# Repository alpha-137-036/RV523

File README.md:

# RV523
An implementation of a Risc-V CPU using only discrete transistors in SOT-523 packages.

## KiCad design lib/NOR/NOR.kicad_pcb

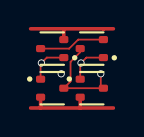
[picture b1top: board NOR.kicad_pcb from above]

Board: 2 copper layers, 4 parts (0 on the bottom side), 5 nets.

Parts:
N1, N2: SOT-523
P1, P2: SOT-523

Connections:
A: N1.1 (G), P1.1 (G)
B: N2.1 (G), P2.1 (G)
C: P1.3 (D), P2.2 (S)
GND: N1.2 (S), N2.2 (S)
Y: N1.3 (D), N2.3 (D), P2.3 (D)

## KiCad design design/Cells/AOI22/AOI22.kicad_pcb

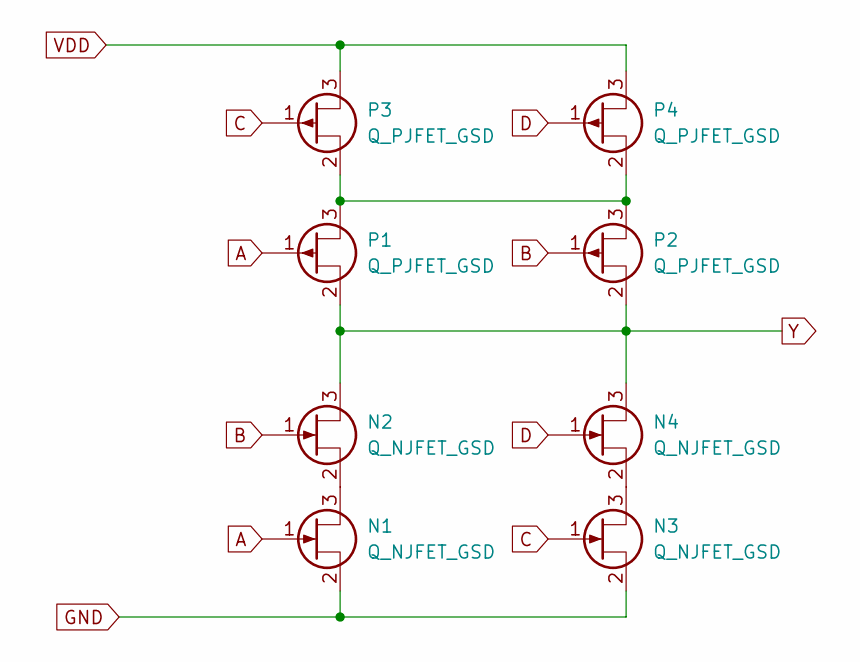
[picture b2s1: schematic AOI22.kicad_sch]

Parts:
N1, N2, N3, N4: Q_NJFET_GSD; SOT-523
P1, P2, P3, P4: Q_PJFET_GSD; SOT-523

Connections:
A: N1.1 (G), P1.1 (G)
B: N2.1 (G), P2.1 (G)
C: N3.1 (G), P3.1 (G)
D: N4.1 (G), P4.1 (G)
GND: N1.2 (S), N3.2 (S)
unnamed: N1.3 (D), N2.2 (S)
unnamed: N3.3 (D), N4.2 (S)
unnamed: P1.3 (D), P2.3 (D), P3.2 (S), P4.2 (S)
VDD: P3.3 (D), P4.3 (D)
Y: N2.3 (D), N4.3 (D), P1.2 (S), P2.2 (S)

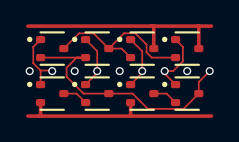
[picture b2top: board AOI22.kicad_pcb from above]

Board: 2 copper layers, 8 parts (0 on the bottom side), 10 nets.

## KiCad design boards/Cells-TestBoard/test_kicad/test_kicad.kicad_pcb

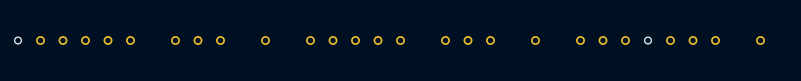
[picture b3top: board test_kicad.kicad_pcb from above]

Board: 4 copper layers, 8 parts (0 on the bottom side), 9 nets.

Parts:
XAxB: AOI22
XCin: NOT
XS: NOT
XnA: NOT
XnAxB: NOT
XnB: NOT
XnCout: AOI22
XnS: AOI22

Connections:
unnamed: XAxB.A, XnA.A, XnCout.A
unnamed: XAxB.B, XnB.A, XnCout.B
unnamed: XCin.A, XnS.B
unnamed: XAxB.C, XnA.Y
unnamed: XAxB.D, XnB.Y
unnamed: XAxB.Y, XnAxB.A, XnCout.D, XnS.A
unnamed: XCin.Y, XnCout.C, XnS.D
unnamed: XS.A, XnS.Y
unnamed: XnAxB.Y, XnS.C

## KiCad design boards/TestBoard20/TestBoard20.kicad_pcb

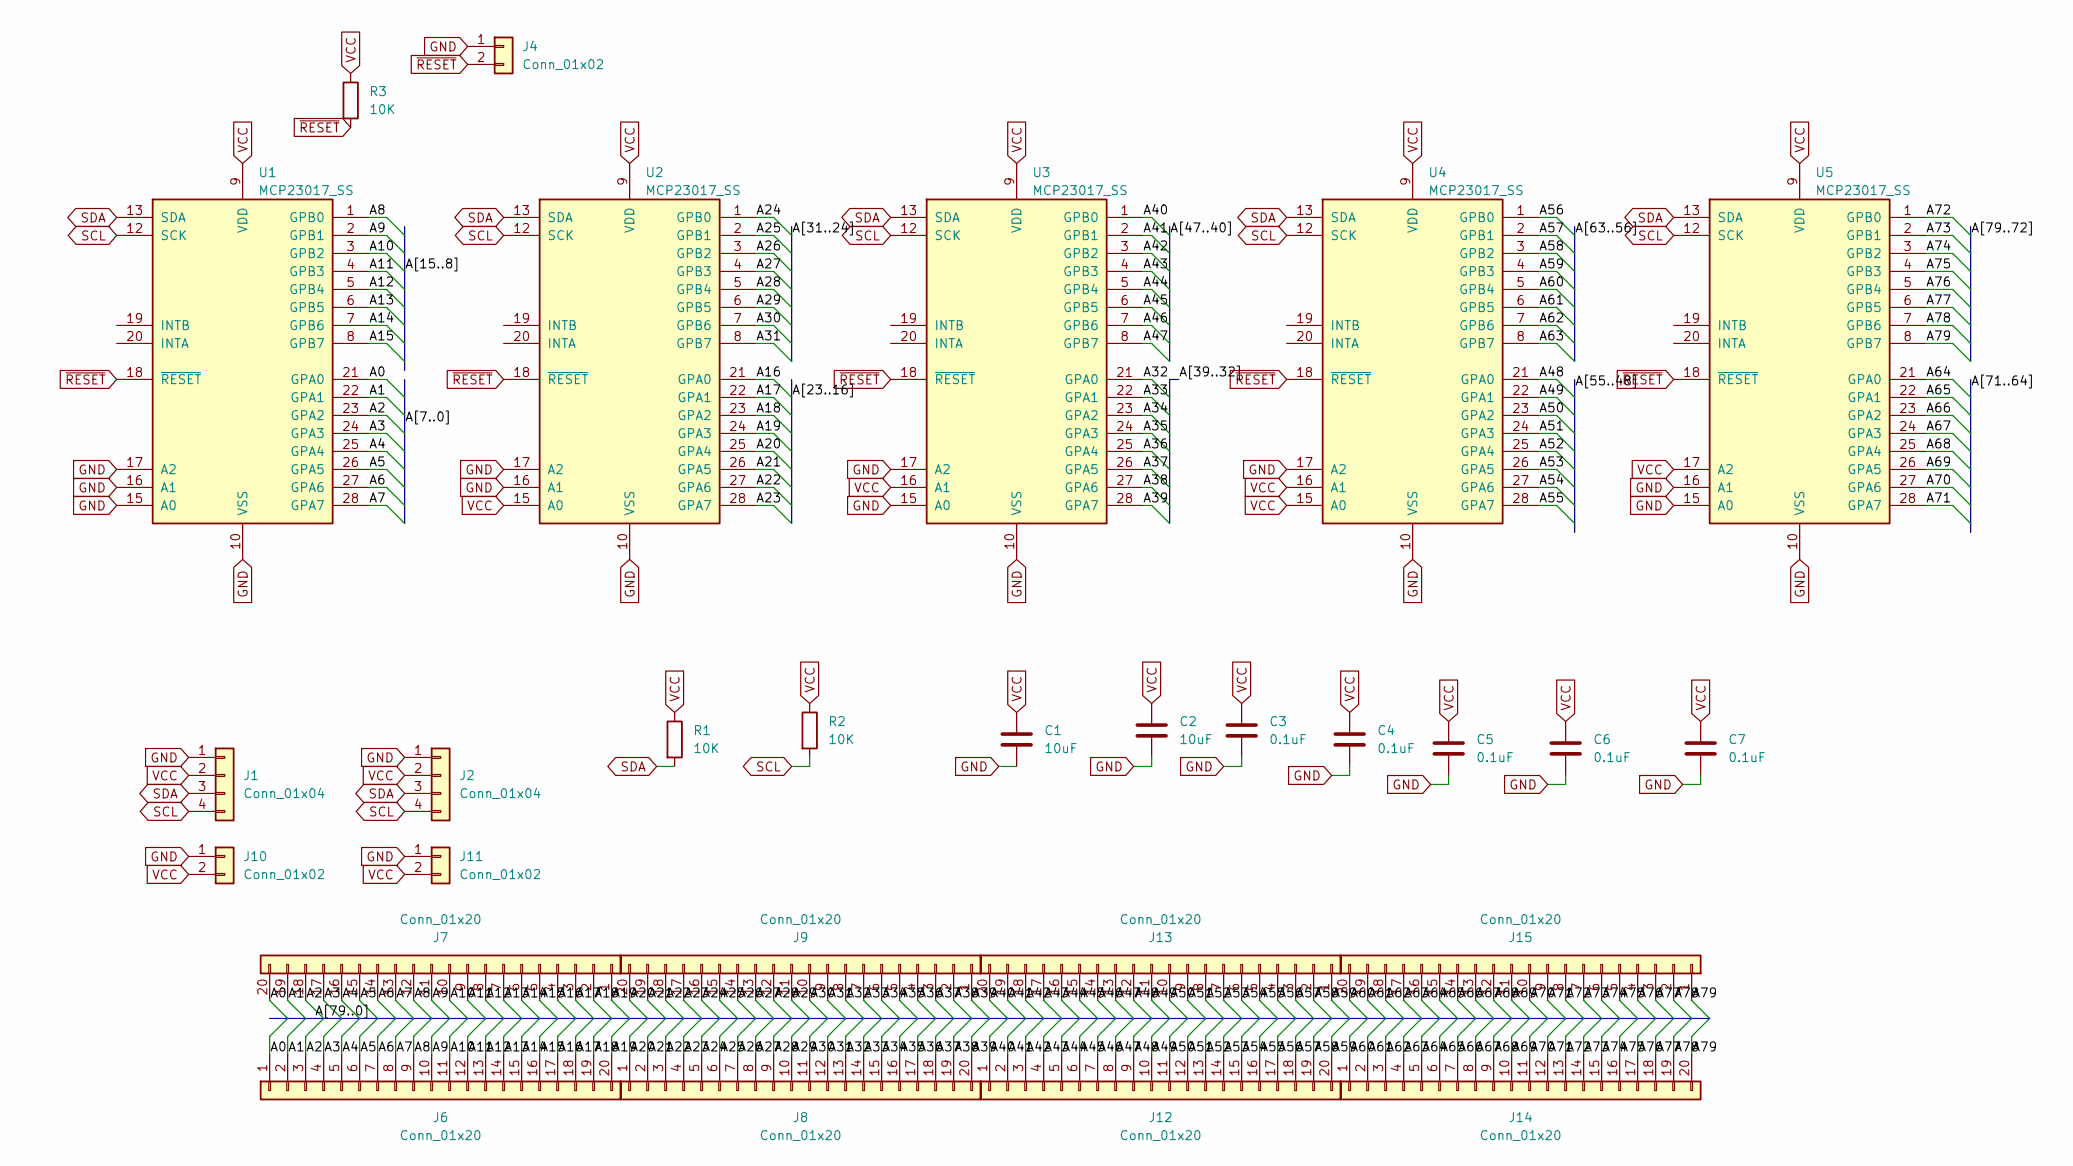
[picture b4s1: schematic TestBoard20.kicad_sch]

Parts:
C1, C2: 10uF; C_0402_1005Metric; LCSC C15525
C3, C4, C5, C6, C7: 0.1uF; C_0402_1005Metric; LCSC C1525
J1, J2: Conn_01x04; JST_SH_SM04B-SRSS-TB_1x04-1MP_P1.00mm_Horizontal; LCSC C160404
J4, J10, J11: Conn_01x02; PinHeader_1x02_P2.54mm_Vertical
J6, J7, J8, J9, J12, J13, J14, J15: Conn_01x20; FFC-SMD_FFC05021-20SBB123W5M; LCSC C19267987
R1, R2, R3: 10K; R_0402_1005Metric; LCSC C25744
U1, U2, U3, U4, U5: MCP23017_SS; SSOP-28_5.3x10.2mm_P0.65mm; LCSC C558584

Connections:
/A0: J6.1, J7.20, U1.21 (GPA0)
/A1: J6.2, J7.19, U1.22 (GPA1)
/A2: J6.3, J7.18, U1.23 (GPA2)
/A3: J6.4, J7.17, U1.24 (GPA3)
/A4: J6.5, J7.16, U1.25 (GPA4)
/A5: J6.6, J7.15, U1.26 (GPA5)
/A6: J6.7, J7.14, U1.27 (GPA6)
/A7: J6.8, J7.13, U1.28 (GPA7)
/A8: J6.9, J7.12, U1.1 (GPB0)
/A9: J6.10, J7.11, U1.2 (GPB1)
/A10: J6.11, J7.10, U1.3 (GPB2)
/A11: J6.12, J7.9, U1.4 (GPB3)
/A12: J6.13, J7.8, U1.5 (GPB4)
/A13: J6.14, J7.7, U1.6 (GPB5)
/A14: J6.15, J7.6, U1.7 (GPB6)
/A15: J6.16, J7.5, U1.8 (GPB7)
/A16: J6.17, J7.4, U2.21 (GPA0)
/A17: J6.18, J7.3, U2.22 (GPA1)
/A18: J6.19, J7.2, U2.23 (GPA2)
/A19: J6.20, J7.1, U2.24 (GPA3)
/A20: J8.1, J9.20, U2.25 (GPA4)
/A21: J8.2, J9.19, U2.26 (GPA5)
/A22: J8.3, J9.18, U2.27 (GPA6)
/A23: J8.4, J9.17, U2.28 (GPA7)
/A24: J8.5, J9.16, U2.1 (GPB0)
/A25: J8.6, J9.15, U2.2 (GPB1)
/A26: J8.7, J9.14, U2.3 (GPB2)
/A27: J8.8, J9.13, U2.4 (GPB3)
/A28: J8.9, J9.12, U2.5 (GPB4)
/A29: J8.10, J9.11, U2.6 (GPB5)
/A30: J8.11, J9.10, U2.7 (GPB6)
/A31: J8.12, J9.9, U2.8 (GPB7)
/A32: J8.13, J9.8, U3.21 (GPA0)
/A33: J8.14, J9.7, U3.22 (GPA1)
/A34: J8.15, J9.6, U3.23 (GPA2)
/A35: J8.16, J9.5, U3.24 (GPA3)
/A36: J8.17, J9.4, U3.25 (GPA4)
/A37: J8.18, J9.3, U3.26 (GPA5)
/A38: J8.19, J9.2, U3.27 (GPA6)
/A39: J8.20, J9.1, U3.28 (GPA7)
/A40: J12.1, J13.20, U3.1 (GPB0)
/A41: J12.2, J13.19, U3.2 (GPB1)
/A42: J12.3, J13.18, U3.3 (GPB2)
/A43: J12.4, J13.17, U3.4 (GPB3)
/A44: J12.5, J13.16, U3.5 (GPB4)
/A45: J12.6, J13.15, U3.6 (GPB5)
/A46: J12.7, J13.14, U3.7 (GPB6)
/A47: J12.8, J13.13, U3.8 (GPB7)
/A48: J12.9, J13.12, U4.21 (GPA0)
/A49: J12.10, J13.11, U4.22 (GPA1)
/A50: J12.11, J13.10, U4.23 (GPA2)
/A51: J12.12, J13.9, U4.24 (GPA3)
/A52: J12.13, J13.8, U4.25 (GPA4)
/A53: J12.14, J13.7, U4.26 (GPA5)
/A54: J12.15, J13.6, U4.27 (GPA6)
/A55: J12.16, J13.5, U4.28 (GPA7)
/A56: J12.17, J13.4, U4.1 (GPB0)
/A57: J12.18, J13.3, U4.2 (GPB1)
/A58: J12.19, J13.2, U4.3 (GPB2)
/A59: J12.20, J13.1, U4.4 (GPB3)
/A60: J14.1, J15.20, U4.5 (GPB4)
/A61: J14.2, J15.19, U4.6 (GPB5)
/A62: J14.3, J15.18, U4.7 (GPB6)
/A63: J14.4, J15.17, U4.8 (GPB7)
/A64: J14.5, J15.16, U5.21 (GPA0)
/A65: J14.6, J15.15, U5.22 (GPA1)
/A66: J14.7, J15.14, U5.23 (GPA2)
/A67: J14.8, J15.13, U5.24 (GPA3)
/A68: J14.9, J15.12, U5.25 (GPA4)
/A69: J14.10, J15.11, U5.26 (GPA5)
/A70: J14.11, J15.10, U5.27 (GPA6)
/A71: J14.12, J15.9, U5.28 (GPA7)
/A72: J14.13, J15.8, U5.1 (GPB0)
/A73: J14.14, J15.7, U5.2 (GPB1)
/A74: J14.15, J15.6, U5.3 (GPB2)
/A75: J14.16, J15.5, U5.4 (GPB3)
/A76: J14.17, J15.4, U5.5 (GPB4)
/A77: J14.18, J15.3, U5.6 (GPB5)
/A78: J14.19, J15.2, U5.7 (GPB6)
/A79: J14.20, J15.1, U5.8 (GPB7)
GND: C1.2, C2.2, C3.2, C4.2, C5.2, C6.2, C7.2, J1.1, J2.1, J4.1, J10.1, J11.1, U1.10 (VSS), U1.15 (A0), U1.16 (A1), U1.17 (A2), U2.10 (VSS), U2.16 (A1), U2.17 (A2), U3.10 (VSS), U3.15 (A0), U3.17 (A2), U4.10 (VSS), U4.17 (A2), U5.10 (VSS), U5.15 (A0), U5.16 (A1); also elsewhere on the board
SCL: J1.4, J2.4, R2.2, U1.12 (SCK), U2.12 (SCK), U3.12 (SCK), U4.12 (SCK), U5.12 (SCK)
SDA: J1.3, J2.3, R1.2, U1.13 (SDA), U2.13 (SDA), U3.13 (SDA), U4.13 (SDA), U5.13 (SDA)
VCC: C1.1, C2.1, C3.1, C4.1, C5.1, C6.1, C7.1, J1.2, J2.2, J10.2, J11.2, R1.1, R2.1, R3.1, U1.9 (VDD), U2.9 (VDD), U2.15 (A0), U3.9 (VDD), U3.16 (A1), U4.9 (VDD), U4.15 (A0), U4.16 (A1), U5.9 (VDD), U5.17 (A2)
~RESET: J4.2, R3.2, U1.18 (~RESET), U2.18 (~RESET), U3.18 (~RESET), U4.18 (~RESET), U5.18 (~RESET)

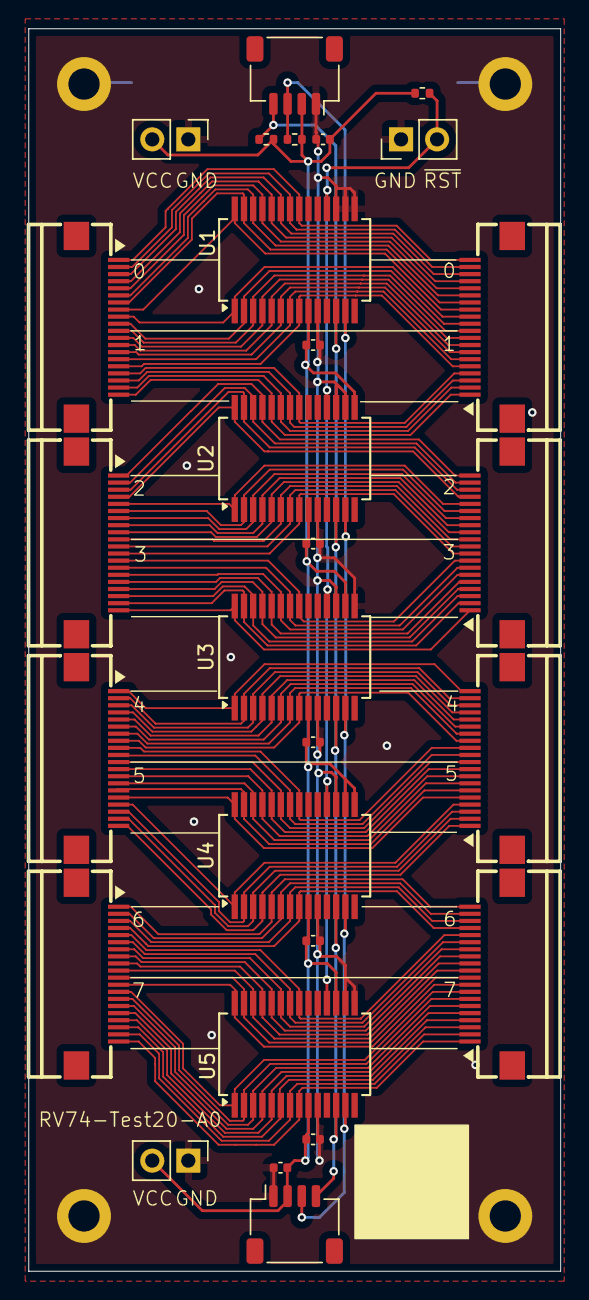
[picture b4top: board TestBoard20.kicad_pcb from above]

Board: 2 copper layers, 37.5 x 87.6 mm, 32 parts (0 on the bottom side), 85 nets.

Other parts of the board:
GND: MountingHole_2.2mm_M2_ISO14580_Pad
GND#2, GND#3, GND#4: MountingHole_2.2mm_M2_ISO14580_Pad

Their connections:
GND: GND.1, GND#2.1, GND#3.1, GND#4.1; also elsewhere on the board

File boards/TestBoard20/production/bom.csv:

Designator,Footprint,Quantity,Value,LCSC Part #
"C1, C2",0402,2,10uF,C15525
"C3, C4, C5, C6, C7",0402,5,0.1uF,C1525
"J1, J2",JST_SH_SM04B-SRSS-TB_1x04-1MP_P1.00mm_Horizontal,2,Conn_01x04,C160404
"J12, J13, J14, J15, J6, J7, J8, J9",FFC-SMD_FFC05021-20SBB123W5M,8,Conn_01x20,C19267987
"R1, R2, R3",0402,3,10K,C25744
"U1, U2, U3, U4, U5",SSOP-28_5.3x10.2mm_P0.65mm,5,MCP23017_SS,C558584

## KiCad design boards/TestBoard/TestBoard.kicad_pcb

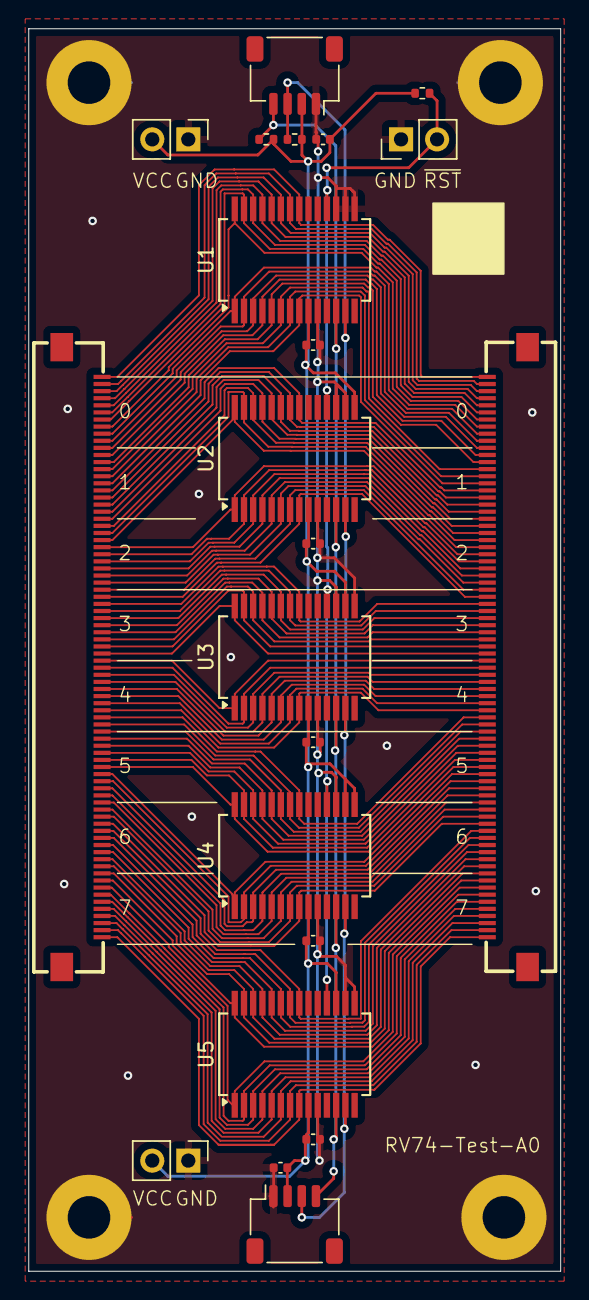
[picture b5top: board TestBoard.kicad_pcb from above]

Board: 2 copper layers, 37.5 x 87.6 mm, 26 parts (0 on the bottom side), 85 nets.

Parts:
C1, C2: 10uF; C_0402_1005Metric
C3, C4, C5, C6, C7: 0.1uF; C_0402_1005Metric
H1, H2, H3, H4: MountingHole_3mm_Pad
J1, J2: Conn_01x04; JST_SH_SM04B-SRSS-TB_1x04-1MP_P1.00mm_Horizontal
J3, J5: Conn_01x80; FPC-SMD_THD0518-80CL-GF
J4, J10, J11: Conn_01x02; PinHeader_1x02_P2.54mm_Vertical
R1, R2, R3: 10K; R_0402_1005Metric
U1, U2, U3, U4, U5: MCP23017_SS; SSOP-28_5.3x10.2mm_P0.65mm

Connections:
/A0: J3.1, J5.80, U1.21 (GPA0)
/A1: J3.2, J5.79, U1.22 (GPA1)
/A2: J3.3, J5.78, U1.23 (GPA2)
/A3: J3.4, J5.77, U1.24 (GPA3)
/A4: J3.5, J5.76, U1.25 (GPA4)
/A5: J3.6, J5.75, U1.26 (GPA5)
/A6: J3.7, J5.74, U1.27 (GPA6)
/A7: J3.8, J5.73, U1.28 (GPA7)
/A8: J3.9, J5.72, U1.1 (GPB0)
/A9: J3.10, J5.71, U1.2 (GPB1)
/A10: J3.11, J5.70, U1.3 (GPB2)
/A11: J3.12, J5.69, U1.4 (GPB3)
/A12: J3.13, J5.68, U1.5 (GPB4)
/A13: J3.14, J5.67, U1.6 (GPB5)
/A14: J3.15, J5.66, U1.7 (GPB6)
/A15: J3.16, J5.65, U1.8 (GPB7)
/A16: J3.17, J5.64, U2.21 (GPA0)
/A17: J3.18, J5.63, U2.22 (GPA1)
/A18: J3.19, J5.62, U2.23 (GPA2)
/A19: J3.20, J5.61, U2.24 (GPA3)
/A20: J3.21, J5.60, U2.25 (GPA4)
/A21: J3.22, J5.59, U2.26 (GPA5)
/A22: J3.23, J5.58, U2.27 (GPA6)
/A23: J3.24, J5.57, U2.28 (GPA7)
/A24: J3.25, J5.56, U2.1 (GPB0)
/A25: J3.26, J5.55, U2.2 (GPB1)
/A26: J3.27, J5.54, U2.3 (GPB2)
/A27: J3.28, J5.53, U2.4 (GPB3)
/A28: J3.29, J5.52, U2.5 (GPB4)
/A29: J3.30, J5.51, U2.6 (GPB5)
/A30: J3.31, J5.50, U2.7 (GPB6)
/A31: J3.32, J5.49, U2.8 (GPB7)
/A32: J3.33, J5.48, U3.21 (GPA0)
/A33: J3.34, J5.47, U3.22 (GPA1)
/A34: J3.35, J5.46, U3.23 (GPA2)
/A35: J3.36, J5.45, U3.24 (GPA3)
/A36: J3.37, J5.44, U3.25 (GPA4)
/A37: J3.38, J5.43, U3.26 (GPA5)
/A38: J3.39, J5.42, U3.27 (GPA6)
/A39: J3.40, J5.41, U3.28 (GPA7)
/A40: J3.41, J5.40, U3.1 (GPB0)
/A41: J3.42, J5.39, U3.2 (GPB1)
/A42: J3.43, J5.38, U3.3 (GPB2)
/A43: J3.44, J5.37, U3.4 (GPB3)
/A44: J3.45, J5.36, U3.5 (GPB4)
/A45: J3.46, J5.35, U3.6 (GPB5)
/A46: J3.47, J5.34, U3.7 (GPB6)
/A47: J3.48, J5.33, U3.8 (GPB7)
/A48: J3.49, J5.32, U4.21 (GPA0)
/A49: J3.50, J5.31, U4.22 (GPA1)
/A50: J3.51, J5.30, U4.23 (GPA2)
/A51: J3.52, J5.29, U4.24 (GPA3)
/A52: J3.53, J5.28, U4.25 (GPA4)
/A53: J3.54, J5.27, U4.26 (GPA5)
/A54: J3.55, J5.26, U4.27 (GPA6)
/A55: J3.56, J5.25, U4.28 (GPA7)
/A56: J3.57, J5.24, U4.1 (GPB0)
/A57: J3.58, J5.23, U4.2 (GPB1)
/A58: J3.59, J5.22, U4.3 (GPB2)
/A59: J3.60, J5.21, U4.4 (GPB3)
/A60: J3.61, J5.20, U4.5 (GPB4)
/A61: J3.62, J5.19, U4.6 (GPB5)
/A62: J3.63, J5.18, U4.7 (GPB6)
/A63: J3.64, J5.17, U4.8 (GPB7)
/A64: J3.65, J5.16, U5.21 (GPA0)
/A65: J3.66, J5.15, U5.22 (GPA1)
/A66: J3.67, J5.14, U5.23 (GPA2)
/A67: J3.68, J5.13, U5.24 (GPA3)
/A68: J3.69, J5.12, U5.25 (GPA4)
/A69: J3.70, J5.11, U5.26 (GPA5)
/A70: J3.71, J5.10, U5.27 (GPA6)
/A71: J3.72, J5.9, U5.28 (GPA7)
/A72: J3.73, J5.8, U5.1 (GPB0)
/A73: J3.74, J5.7, U5.2 (GPB1)
/A74: J3.75, J5.6, U5.3 (GPB2)
/A75: J3.76, J5.5, U5.4 (GPB3)
/A76: J3.77, J5.4, U5.5 (GPB4)
/A77: J3.78, J5.3, U5.6 (GPB5)
/A78: J3.79, J5.2, U5.7 (GPB6)
/A79: J3.80, J5.1, U5.8 (GPB7)
GND: C1.2, C2.2, C3.2, C4.2, C5.2, C6.2, C7.2, H1.1, H2.1, H3.1, H4.1, J1.1, J2.1, J4.1, J10.1, J11.1, U1.10 (VSS), U1.15 (A0), U1.16 (A1), U1.17 (A2), U2.10 (VSS), U2.16 (A1), U2.17 (A2), U3.10 (VSS), U3.15 (A0), U3.17 (A2), U4.10 (VSS), U4.17 (A2), U5.10 (VSS), U5.15 (A0), U5.16 (A1)
SCL: J1.4, J2.4, R2.2, U1.12 (SCK), U2.12 (SCK), U3.12 (SCK), U4.12 (SCK), U5.12 (SCK)
SDA: J1.3, J2.3, R1.2, U1.13 (SDA), U2.13 (SDA), U3.13 (SDA), U4.13 (SDA), U5.13 (SDA)
VCC: C1.1, C2.1, C3.1, C4.1, C5.1, C6.1, C7.1, J1.2, J2.2, J10.2, J11.2, R1.1, R2.1, R3.1, U1.9 (VDD), U2.9 (VDD), U2.15 (A0), U3.9 (VDD), U3.16 (A1), U4.9 (VDD), U4.15 (A0), U4.16 (A1), U5.9 (VDD), U5.17 (A2)
~RESET: J4.2, R3.2, U1.18 (~RESET), U2.18 (~RESET), U3.18 (~RESET), U4.18 (~RESET), U5.18 (~RESET)

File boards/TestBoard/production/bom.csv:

Designator,Footprint,Quantity,Value,LCSC Part #
"C1, C2",0402,2,10uF,C15525
"C3, C4, C5, C6, C7",0402,5,0.1uF,C1525
"J1, J2",JST_SH_SM04B-SRSS-TB_1x04-1MP_P1.00mm_Horizontal,2,Conn_01x04,C160404
"J3, J5",FPC-SMD_THD0518-80CL-GF,2,Conn_01x80,C283193
"R1, R2, R3",0402,3,10K,C25744
"U1, U2, U3, U4, U5",SSOP-28_5.3x10.2mm_P0.65mm,5,MCP23017_SS,C558584

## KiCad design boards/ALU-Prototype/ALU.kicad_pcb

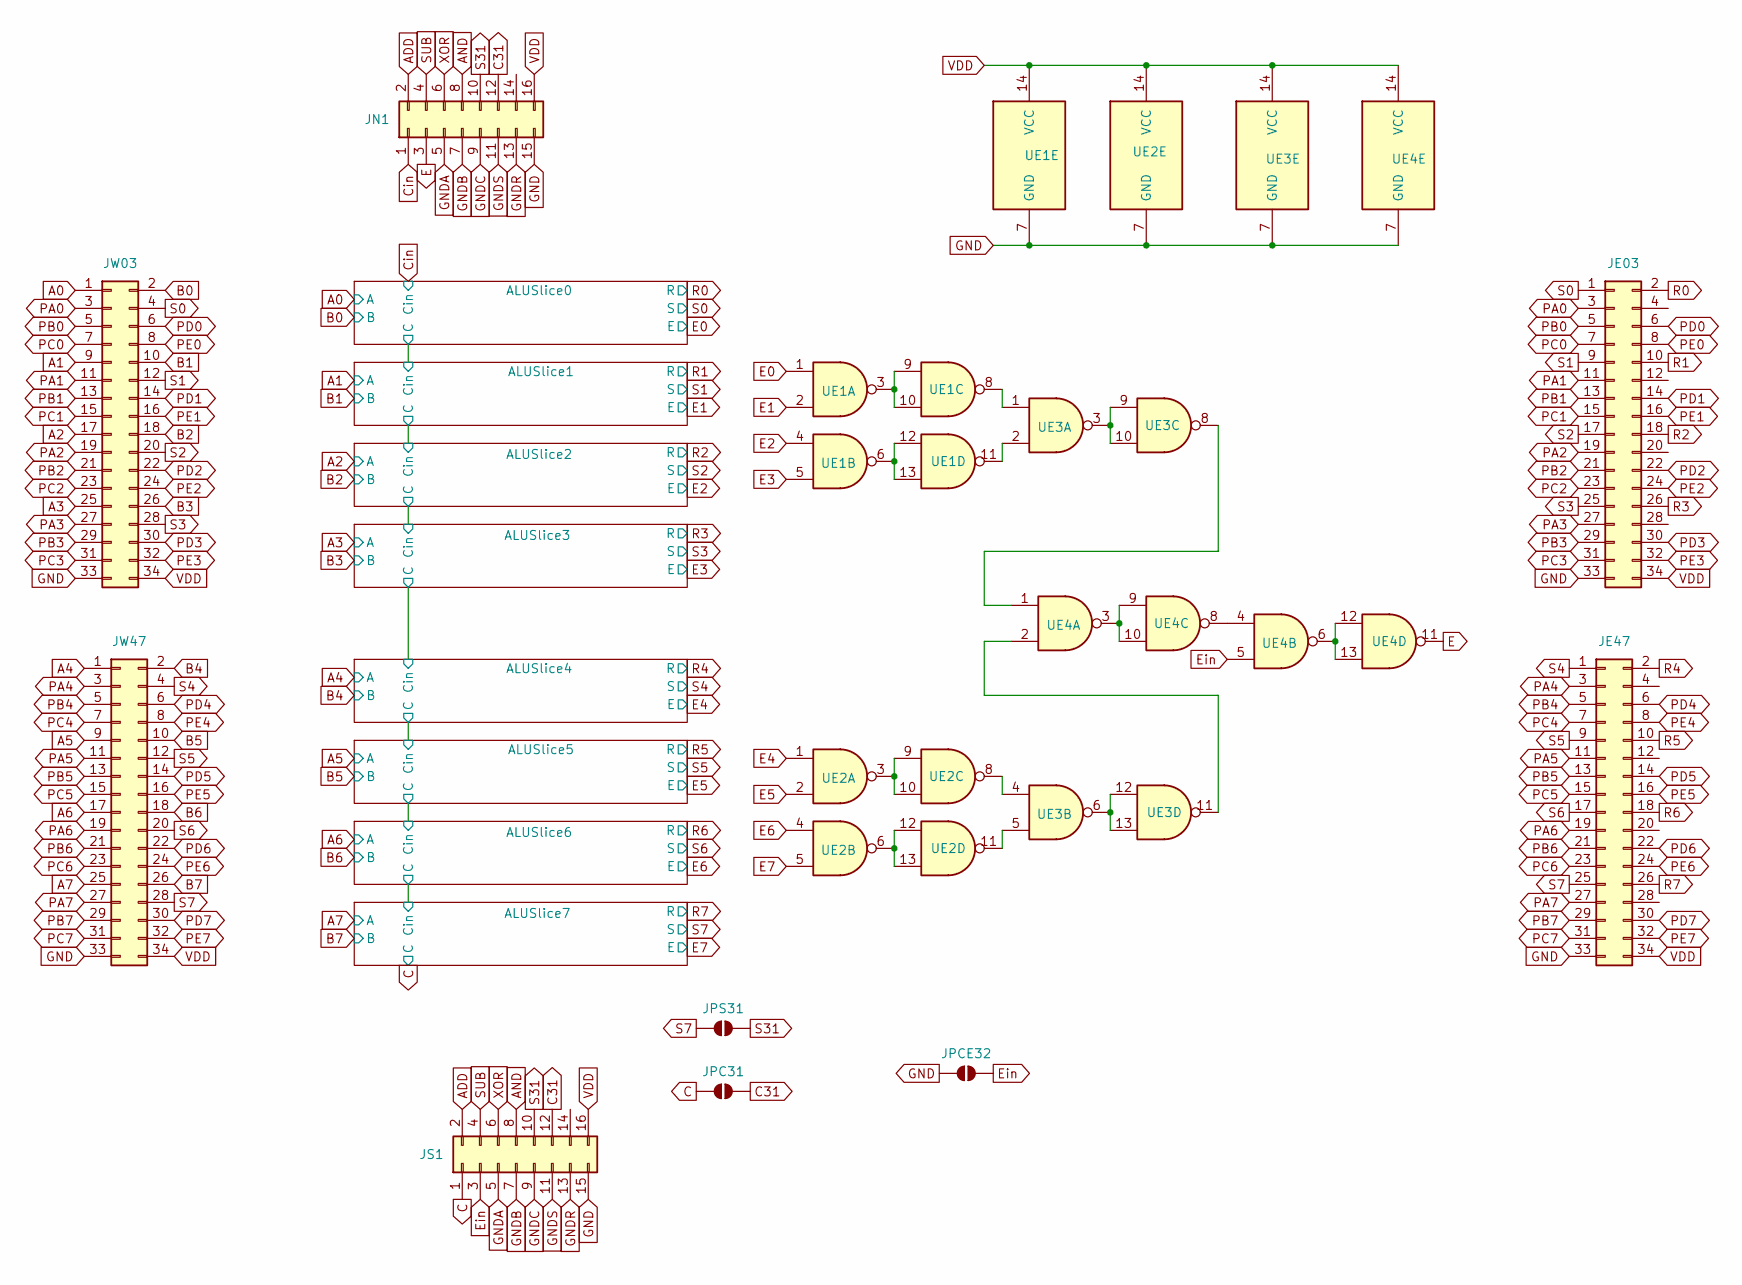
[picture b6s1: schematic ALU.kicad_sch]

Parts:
JE03, JE47: PinHeader_2x17_P2.54mm_Vertical
JN1: PinHeader_2x08_P2.54mm_Vertical
JPC31: SolderJumper_2_Open; SolderJumper-2_P1.3mm_Open_Pad1.0x1.5mm
JPCE32: SolderJumper_2_Open; SolderJumper-2_P1.3mm_Open_Pad1.0x1.5mm
JPS31: SolderJumper_2_Open; SolderJumper-2_P1.3mm_Open_Pad1.0x1.5mm
JS1: PinHeader_2x08_P2.54mm_Vertical
JW03, JW47: PinHeader_2x17_P2.54mm_Vertical
UE1, UE2, UE3, UE4: TSSOP-14_4.4x5mm_P0.65mm; LCSC C5587

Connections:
!SET0: JN1.14, JS1.14; also elsewhere on the board
A0: JW03.1; also elsewhere on the board
A1: JW03.9; also elsewhere on the board
A2: JW03.17; also elsewhere on the board
A3: JW03.25; also elsewhere on the board
A4: JW47.1; also elsewhere on the board
A5: JW47.9; also elsewhere on the board
A6: JW47.17; also elsewhere on the board
A7: JW47.25; also elsewhere on the board
ADD: JN1.2, JS1.2; also elsewhere on the board
AND: JN1.8, JS1.8; also elsewhere on the board
B0: JW03.2; also elsewhere on the board
B1: JW03.10; also elsewhere on the board
B2: JW03.18; also elsewhere on the board
B3: JW03.26; also elsewhere on the board
B4: JW47.2; also elsewhere on the board
B5: JW47.10; also elsewhere on the board
B6: JW47.18; also elsewhere on the board
B7: JW47.26; also elsewhere on the board
C: JPC31.1 (A), JS1.1; also elsewhere on the board
C31: JN1.12, JPC31.2 (B), JS1.12
Cin: JN1.1; also elsewhere on the board
E: JN1.3, UE4.11
E0: UE1.1; also elsewhere on the board
E1: UE1.2; also elsewhere on the board
E2: UE1.4; also elsewhere on the board
E3: UE1.5; also elsewhere on the board
E4: UE2.1; also elsewhere on the board
E5: UE2.2; also elsewhere on the board
E6: UE2.4; also elsewhere on the board
E7: UE2.5; also elsewhere on the board
Ein: JPCE32.2 (B), JS1.3, UE4.5; also elsewhere on the board
GND: JE03.33, JE47.33, JN1.15, JPCE32.1 (A), JS1.15, JW03.33, JW47.33, UE1.7 (GND), UE2.7 (GND), UE3.7 (GND), UE4.7 (GND); also elsewhere on the board
GNDA: JN1.5, JS1.5; also elsewhere on the board
GNDB: JN1.7, JS1.7; also elsewhere on the board
GNDC: JN1.9, JS1.9; also elsewhere on the board
GNDR: JN1.13, JS1.13; also elsewhere on the board
GNDS: JN1.11, JS1.11; also elsewhere on the board
unnamed: UE1.8, UE3.1
unnamed: UE1.3, UE1.9, UE1.10
unnamed: UE1.11, UE3.2
unnamed: UE1.6, UE1.12, UE1.13
unnamed: UE2.8, UE3.4
unnamed: UE2.3, UE2.9, UE2.10
unnamed: UE2.11, UE3.5
unnamed: UE2.6, UE2.12, UE2.13
unnamed: UE3.8, UE4.1
unnamed: UE3.3, UE3.9, UE3.10
unnamed: UE3.11, UE4.2
unnamed: UE3.6, UE3.12, UE3.13
unnamed: UE4.4, UE4.8
unnamed: UE4.3, UE4.9, UE4.10
unnamed: UE4.6, UE4.12, UE4.13
PA0: JE03.3, JW03.3
PA1: JE03.11, JW03.11
PA2: JE03.19, JW03.19
PA3: JE03.27, JW03.27
PA4: JE47.3, JW47.3
PA5: JE47.11, JW47.11
PA6: JE47.19, JW47.19
PA7: JE47.27, JW47.27
PB0: JE03.5, JW03.5
PB1: JE03.13, JW03.13
PB2: JE03.21, JW03.21
PB3: JE03.29, JW03.29
PB4: JE47.5, JW47.5
PB5: JE47.13, JW47.13
PB6: JE47.21, JW47.21
PB7: JE47.29, JW47.29
PC0: JE03.7, JW03.7
PC1: JE03.15, JW03.15
PC2: JE03.23, JW03.23
PC3: JE03.31, JW03.31
PC4: JE47.7, JW47.7
PC5: JE47.15, JW47.15
PC6: JE47.23, JW47.23
PC7: JE47.31, JW47.31
PD0: JE03.6, JW03.6
PD1: JE03.14, JW03.14
PD2: JE03.22, JW03.22
PD3: JE03.30, JW03.30
PD4: JE47.6, JW47.6
PD5: JE47.14, JW47.14
PD6: JE47.22, JW47.22
PD7: JE47.30, JW47.30
PE0: JE03.8, JW03.8
PE1: JE03.16, JW03.16
PE2: JE03.24, JW03.24
PE3: JE03.32, JW03.32
PE4: JE47.8, JW47.8
PE5: JE47.16, JW47.16
PE6: JE47.24, JW47.24
PE7: JE47.32, JW47.32
R0: JE03.2; also elsewhere on the board
R1: JE03.10; also elsewhere on the board
R2: JE03.18; also elsewhere on the board
R3: JE03.26; also elsewhere on the board
R4: JE47.2; also elsewhere on the board
R5: JE47.10; also elsewhere on the board
R6: JE47.18; also elsewhere on the board
R7: JE47.26; also elsewhere on the board
S0: JE03.1, JW03.4; also elsewhere on the board
S1: JE03.9, JW03.12; also elsewhere on the board
S2: JE03.17, JW03.20; also elsewhere on the board
S3: JE03.25, JW03.28; also elsewhere on the board
S4: JE47.1, JW47.4; also elsewhere on the board
S5: JE47.9, JW47.12; also elsewhere on the board
S6: JE47.17, JW47.20; also elsewhere on the board
S7: JE47.25, JPS31.1 (A), JW47.28; also elsewhere on the board
S31: JN1.10, JPS31.2 (B), JS1.10
SUB: JN1.4, JS1.4; also elsewhere on the board
VDD: JE03.34, JE47.34, JN1.16, JS1.16, JW03.34, JW47.34, UE1.14 (VCC), UE2.14 (VCC), UE3.14 (VCC), UE4.14 (VCC); also elsewhere on the board
XOR: JN1.6, JS1.6; also elsewhere on the board
